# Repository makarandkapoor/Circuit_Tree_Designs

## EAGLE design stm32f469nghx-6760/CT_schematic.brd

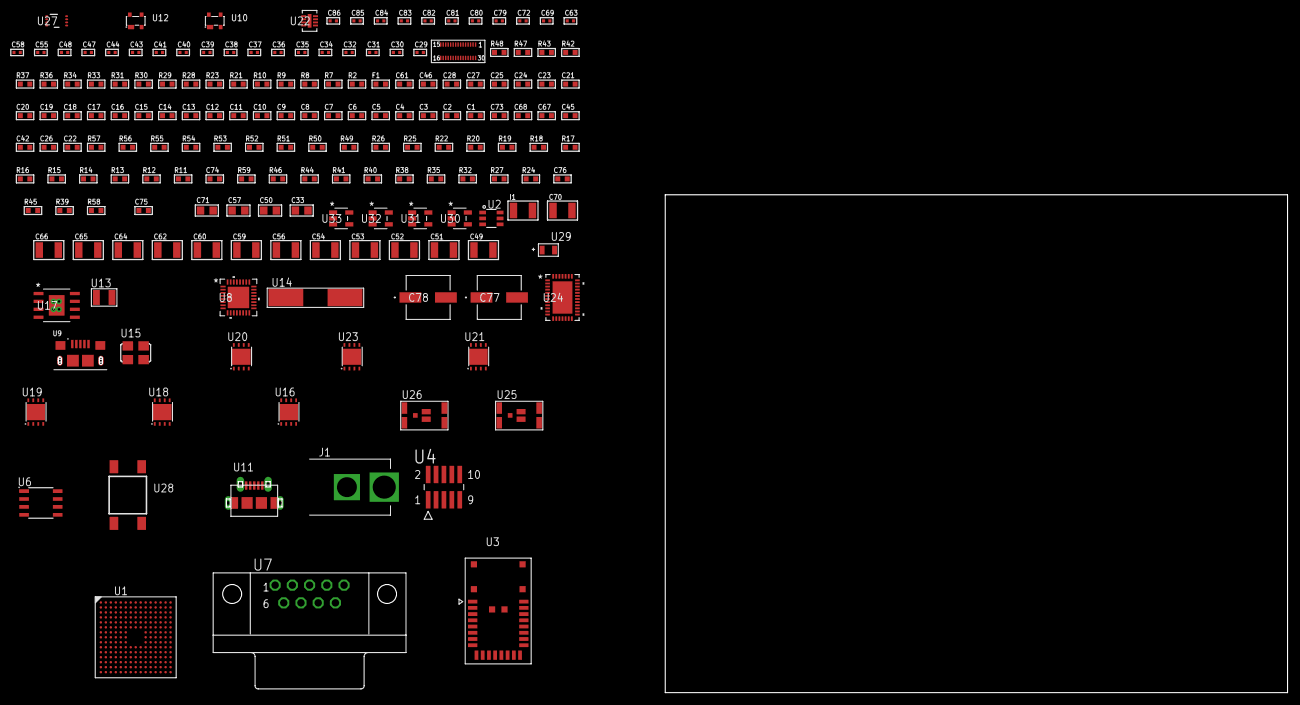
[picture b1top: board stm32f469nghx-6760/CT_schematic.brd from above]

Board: 2 copper layers, 176 parts (0 on the bottom side), 114 nets, no tracks yet.

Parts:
C1, C24, C46: 1e-06; C0603
C2, C3, C4, C5, C6, C7, C8, C9, C10, C11, C12, C13, C14, C15, C16, C17, C18, C19, C20, C21, C25, C27, C28: 1e-07; C0603
C22: 4.7e-06; C0603
C23: 1e-08; C0603
C26, C42, C45, C67, C73: 2.2e-06; C0603
C29, C30, C31, C32: 1e-11; C0402
C33, C50, C57, C71: 1e-05; C0805
C34, C35, C36, C37, C38, C39, C40, C41, C43, C44, C72, C80, C82: 1e-07; C0402
C47, C48, C55, C58, C63, C69, C79, C81, C83, C84, C85, C86: 1e-08; C0402
C49, C51, C52, C53, C54, C56, C59, C60, C62, C64, C65, C66, C70: 1e-05; C1210
C61: 8e-07; R0603
C68: 2.2e-07; C0603
C74: 2.45e-08; R0603
C75: 2.8258362168397e-09; R0603
C76: 7.105e-09; R0603
C77, C78: 0.0001; EXV-9H
F1: 240.0; L0603
I1: 1e-05; L1210
J1: PJ-037B; PJ-037B_PACKAGE
R2, R29, R34, R37, R43, R48: 1000.0; R0603
R7, R8, R9: 4700.0; R0603
R10, R31: 2200.0; R0603
R11: 47000.0; R0603
R12, R13, R14, R15, R16, R17, R18, R19, R20, R22, R25, R26, R49, R51, R52, R55, R56, R57: 10000.0; R0603
R21: 5.0; R0603
R23: 120.0; R0603
R24, R27, R32, R35, R38, R40, R41, R44, R46: 100000.0; R0603
R28, R47: 200.0; R0603
R30: 910.0; R0603
R33: 806.0; R0603
R36: 1800.0; R0603
R39: 153694.38; R0603
R42: 3900.0; R0603
R45: 1600000.0; R0603
R50: 75000.0; R0603
R53, R54: 95300.0; R0603
R58: 102454.54545455; R0603
R59: 200000.0; R0603
U1: STM32F469NGH6; TFBGA216
U2: MAX4995AAUT+T; SOT-23-6
U3: A2500R24A00GM
U4: FTSH-105-01-L-DV-K; SAMTEC_FTSH-105-01-L-DV-K
U5: LH430WV2-SD01
U6: SN65HVD230D; SOIC-8
U7: 182-009-113R531; 182-009-MALE
U8: TUSB1210BRHBR; RHB32_3P45X3P45
U9: 10118193-0001LF; FCI_10118193-0001LF
U10, U12: prtr5v0u2ax; SOT143B
U11: 47590-0001; MICRO_USB_AB
U13: ABS07-32.768KHZ-7-T
U14: ABLS-25.000MHZ-B2F-T
U15: ASFL1-26MHZ-NCS; ASFL1
U16, U18, U19, U21, U23: LP3878SDX-ADJ/NOPB; WSON-8
U17: MIC5234YME; SOIC-8_EP
U20: LP2951ACSDX/NOPB; WSON-8
U22: LT3494AEDDB#TRMPBF; DFN-8_DDB
U24: LTC2928CUHF#PBF; QFN-38_UHF
U25, U26: IRF8306MTRPbF; IRF8306MTRPBF
U27: LSF0102DCTR; DCU0008A_N
U28: 4-1437565-2; SW_4-1437565-2
U29: Q65110A2395; LGM67K-G1J2-24-Z
U30, U31, U32, U33: nc7sz125m5x; NC7SZ125M5X

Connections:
CLK_CRYSTAL_U1_E1: C29.1, U1.E1, U13.1
CLK_CRYSTAL_U1_F1: C30.1, U1.F1, U13.2
CLK_CRYSTAL_U1_G1: C31.1, U1.G1, U14.1
CLK_CRYSTAL_U1_H1: C32.1, U1.H1, U14.2
CLK_U8_1: U8.1, U15.3
GND: C1.2, C2.2, C3.2, C4.2, C5.2, C6.2, C7.2, C8.2, C9.2, C10.2, C11.2, C12.2, C13.2, C14.2, C15.2, C16.2, C17.2, C18.2, C19.2, C20.2, C21.2, C22.2, C23.2, C24.2, C25.2, C26.2, C27.2, C28.2, C29.2, C30.2, C31.2, C32.2, C33.2, C34.2, C35.2, C36.2, C37.2, C38.2, C39.2, C40.2, C41.2, C42.2, C43.2, C44.2, C45.2, C46.2, C47.2, C48.2, C49.2, C50.2, C51.2, C52.2, C53.2, C54.2, C55.2, C56.2, C57.2, C58.2, C59.2, C60.2, C61.2, C62.2, C63.2, C64.2, C65.2, C66.2, C67.2, C68.2, C69.2, C70.2, C71.2, C72.2, C73.2, C74.2, C75.2, C76.2, C77.2, C78.2, C79.2, C80.2, C81.2, C82.2, C83.2, C84.2, C85.2, C86.2, J1.2, R2.2, R11.2, R14.2, R17.2, R21.2, R22.2, R24.2, R29.2, R31.2, R34.2, R37.2, R40.2, R43.2, R48.2, R50.2, R53.2, R54.2, R55.2, R56.2, R57.2, U1.F2, U1.F6, U1.F7, U1.F8, U1.F9, U1.F10, U1.G6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
NET_U1_E5: R12.1, U1.E5
NET_U1_E6: R13.1, U1.E6
NET_U1_E11: C28.1, U1.E11
NET_U1_G13: C26.1, U1.G13, U1.K12
NET_U1_J1: R8.1, U1.J1, U32.4
NET_U1_L5: R15.1, U1.L5
NET_U1_M5: R14.1, U1.M5
NET_U1_R1: C23.1, C24.1, F1.1, U1.P1, U1.R1
NET_U1_R15: U28.3, U28.4
NET_U2_3: R11.1, U2.3
NET_U4_9: R21.1, U4.9
NET_U5_4: R7.1, U5.4, U31.4
NET_U5_20: R22.1, U5.20
NET_U6_6: R23.2, U6.6
NET_U6_8: R24.1, U6.8
NET_U7_2: R23.2, U6.6, U7.2
NET_U7_3: R23.1, U6.7, U7.3
NET_U8_11: R25.1, U8.11
NET_U8_12: C45.1, U8.12
NET_U8_14: R26.1, U8.14
NET_U8_20: C42.1, U8.20
NET_U8_27: R9.1, U8.27, U33.4
NET_U9_1: C46.1, U8.22, U9.1, U10.4
NET_U9_2: U8.19, U9.2, U10.3
NET_U9_3: U8.18, U9.3, U10.2
NET_U16_1: C48.1, U16.1
NET_U16_6: R28.2, R29.1, U16.6
NET_U16_8: R27.1, U16.8
NET_U17_4: R30.2, R31.1, U17.4
NET_U18_1: C55.1, U18.1
NET_U18_6: R33.2, R34.1, U18.6
NET_U18_8: R32.1, U18.8
NET_U19_1: C58.1, U19.1
NET_U19_6: R36.2, R37.1, U19.6
NET_U19_8: R35.1, U19.8
NET_U20_5: R38.1, U20.5
NET_U20_7: R39.2, R40.1, U20.7
NET_U21_1: C63.1, U21.1
NET_U21_6: R42.2, R43.1, U21.6
NET_U21_8: R41.1, U21.8
NET_U22_1: I1.1, U22.1
NET_U22_5: R44.1, U22.5
NET_U22_6: R45.1, U22.6
NET_U22_8: C68.1, U22.8
NET_U23_1: C69.1, U23.1
NET_U23_6: R47.2, R48.1, U23.6
NET_U23_8: R46.1, U23.8
NET_U24_3: R56.1, U24.3
NET_U24_6: R53.1, U24.6
NET_U24_7: R54.1, U24.7
NET_U24_16: R55.1, R58.1, U24.16
NET_U24_18: R52.1, U24.18
NET_U24_19: R51.1, U24.19, U24.20
NET_U24_21: R49.1, R50.1, U24.21, U30.4, U31.2, U32.2, U33.2
NET_U24_22: C72.1, R49.2, R51.2, R52.2, U24.11, U24.22
NET_U24_26: C75.1, U24.26
NET_U24_27: C74.1, U24.27
NET_U24_28: C76.1, U24.28
NET_U24_38: R57.1, U24.38
NET_U25_3: U24.2, U25.3
NET_U26_3: U24.37, U26.3
NET_U27_8: R59.1, U27.8
NET_U28_1: R2.1, U28.1, U28.2
PROC_CAN1_RX_TOXCVR: U6.4, U27.5
PROC_CAN1_TX_TOXCVR: U6.1, U27.6
PROC_DSIHOST_CKN: U1.H13, U5.13
PROC_DSIHOST_CKP: U1.H12, U5.14
PROC_DSIHOST_D0N: U1.J13, U5.7
PROC_DSIHOST_D0P: U1.J12, U5.8
PROC_DSIHOST_D1N: U1.F13, U5.10
PROC_DSIHOST_D1P: U1.F12, U5.11
PROC_GPIO_TO_U1_USB_FAULT: R16.1, U1.A2, U2.6
PROC_GPIO_TO_U1_VBUS_EN: R17.1, U1.A1, U2.4
PROC_SPI2_MISO: U1.C14, U3.10
PROC_SPI2_MOSI: U1.C13, U3.11
PROC_SPI2_NSS: U1.E14, U3.12
PROC_SPI2_SCK: U1.C11, U3.9
PROC_SYS_JTCK_SWCLK: R19.1, U1.A14, U4.4
PROC_SYS_JTDO_SWO: U1.A10, U4.6
PROC_SYS_JTMS_SWDIO: R20.1, U1.A15, U4.2
PROC_USB_OTG_FS_DM: U1.C15, U11.2, U12.3
PROC_USB_OTG_FS_DP: U1.B15, U11.3, U12.2
PROC_USB_OTG_FS_ID: U1.D15, U11.4
PROC_USB_OTG_FS_VBUS: U1.E15, U2.1, U11.1, U12.4
PROC_USB_OTG_HS_ULPI_CK: U1.P4, U8.26
PROC_USB_OTG_HS_ULPI_D0: U1.R2, U8.3
PROC_USB_OTG_HS_ULPI_D1: U1.R5, U8.4
PROC_USB_OTG_HS_ULPI_D2: U1.R4, U8.5
PROC_USB_OTG_HS_ULPI_D3: U1.P12, U8.6
PROC_USB_OTG_HS_ULPI_D4: U1.R13, U8.7
PROC_USB_OTG_HS_ULPI_D5: U1.L13, U8.9
PROC_USB_OTG_HS_ULPI_D6: U1.K14, U8.10
PROC_USB_OTG_HS_ULPI_D7: U1.A8, U8.13
PROC_USB_OTG_HS_ULPI_DIR: U1.F3, U8.31
PROC_USB_OTG_HS_ULPI_NXT: U1.H4, U8.2
PROC_USB_OTG_HS_ULPI_STP: U1.M2, U8.29
RST_OUT_U4_JTAG_RST_B: R18.1, U4.10, U30.1
VCC_12V6: C73.1, C77.1, C78.1, J1.1, R58.2, U24.23, U25.1, U25.2, U25.6, U25.7, U26.1, U26.2, U26.6, U26.7
VCC_S1_12V6: C49.1, C51.1, C52.1, C56.1, C59.1, C61.1, C64.1, C66.1, I1.2, R27.2, R32.2, R35.2, R41.2, R44.2, U16.4, U17.5, U17.8, U18.4, U19.4, U20.8, U21.4, U22.3, U22.4, U25.4, U25.5
VCC_S2_12V6: C70.1, R46.2, U23.4, U26.4, U26.5
VCC_TIER1_1V2: C27.1, C50.1, R28.1, U1.L11, U16.5
VCC_TIER1_1V5: C53.1, C54.1, R30.1, U5.29, U17.1
VCC_TIER1_1V8: C1.1, C2.1, C3.1, C4.1, C5.1, C6.1, C7.1, C8.1, C9.1, C10.1, C11.1, C12.1, C13.1, C14.1, C15.1, C16.1, C17.1, C18.1, C19.1, C20.1, C21.1, C22.1, C25.1, C33.1, C34.1, C35.1, C43.1, C44.1, C57.1, C81.1, C82.1, C83.1, C84.1, C85.1, C86.1, F1.2, R7.2, R8.2, R9.2, R10.2, R12.2, R13.2, R15.2, R16.2, R18.2, R19.2, R20.2, R25.2, R26.2, R33.1, U1.C1, U1.E7, U1.E8, U1.E9, U1.E10, U1.F4, U1.F5, U1.F11, U1.G5, U1.G11, U1.H5, U1.H11, U1.J5, U1.J11, U1.K5, U1.K11, U1.L7, U1.L8, U1.L9, U1.L10, U3.18, U4.1, U5.2, U8.28, U8.30, U8.32, U18.5, U27.2, U30.5, U31.5, U32.5, U33.5
VCC_TIER1_2V8: C37.1, C38.1, C39.1, C41.1, C60.1, R36.1, U5.16, U5.21, U5.22, U5.23, U8.21, U19.5
VCC_TIER1_3V3: C40.1, C47.1, C62.1, C79.1, C80.1, R38.2, R39.1, R59.2, U6.3, U15.4, U20.1, U27.7
VCC_TIER1_5V0: C65.1, R42.1, U2.5, U21.5
VCC_TIER1_12V0: C36.1, C67.1, R45.2, U5.30, U22.7
VCC_TIER2_1V2: C71.1, R47.1, U23.5

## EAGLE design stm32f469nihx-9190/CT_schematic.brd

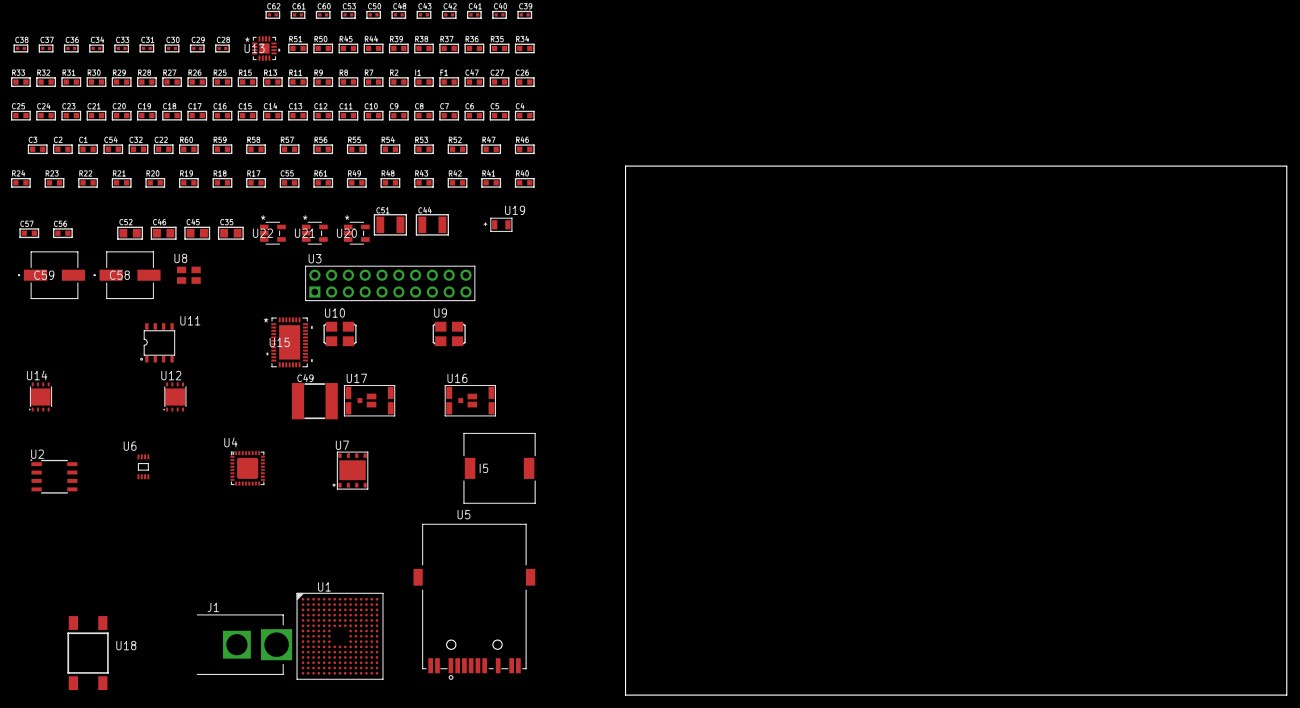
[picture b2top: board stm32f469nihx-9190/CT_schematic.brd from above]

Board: 2 copper layers, 100.0 x 80.0 mm, 140 parts (0 on the bottom side), 95 nets, no tracks yet.

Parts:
C1, C24, C47: 1e-06; C0603
C2, C3, C4, C5, C6, C7, C8, C9, C10, C11, C12, C13, C14, C15, C16, C17, C18, C19, C20, C21, C25, C26, C27: 1e-07; C0603
C22: 4.7e-06; C0603
C23: 1e-08; C0603
C28, C37, C39, C40, C41, C42, C43, C50, C60, C61, C62: 1e-08; C0402
C29, C30, C31, C33, C34, C36, C38, C48, C53: 1e-07; C0402
C32, C54: 2.2e-06; C0603
C35, C45, C46, C52: 1e-05; C0805
C44, C51: 1e-05; C1210
C49: 6.8e-05; 2220
C55: 2.45e-08; R0603
C56: 2.8258362168397e-09; R0603
C57: 7.105e-09; R0603
C58, C59: 0.0001; EXV-9H
F1: 240.0; L0603
I1: 97.0; R0603
I5: 5.2e-06; DR1040
J1: PJ-037B; PJ-037B_PACKAGE
R2, R34, R36, R37, R38, R39, R45, R51: 1000.0; R0603
R7, R8, R30, R31, R32, R33, R35: 4700.0; R0603
R9, R11, R13, R15: 2200.0; R0603
R17, R18, R19, R20, R21, R22, R23, R24, R52, R54, R55, R58, R59, R60: 10000.0; R0603
R25, R26: 0.1; R0603
R27, R44, R50: 200.0; R0603
R28: 220.0; R0603
R29: 6490.0; R0603
R40, R41, R42, R43, R49: 100000.0; R0603
R46: 20000.0; R0603
R47: 91000.0; R0603
R48: 300000.0; R0603
R53: 75000.0; R0603
R56, R57: 95300.0; R0603
R61: 110000.0; R0603
U1: STM32F469NIH6; TFBGA216
U2: AT25512N-SH-T; SOIC-8
U3: TST-110-05-T-D-RA
U4: KSZ8081RNBIA-TR; QFN-32
U5: 7498011122R
U6: 24AA02T-I/MNY; TDFN-8/6MM
U7: SST26VF064B-104I/MF; WFDN-8
U8: ASEK-32.768KHz-ECST; ASEK
U9: ASFL1-25MHZ-NCS; ASFL1
U10: ASFL1-50MHZ-NCS; ASFL1
U11: idt74fct38072; IDT74FCT38072
U12, U14: LP3878SDX-ADJ/NOPB; WSON-8
U13: LTC3601EUD#PBF; QFN-16_EP
U15: LTC2928CUHF#PBF; QFN-38_UHF
U16, U17: IRF8306MTRPbF; IRF8306MTRPBF
U18: 4-1437565-2; SW_4-1437565-2
U19: Q65110A2395; LGM67K-G1J2-24-Z
U20, U21, U22: nc7sz125m5x; NC7SZ125M5X

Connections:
CLK_U1_E1: U1.E1, U8.3
CLK_U1_G1: U1.G1, U9.3
CLK_U1_N2: U1.N2, U11.7
CLK_U4_9: U4.9, U11.6
CLK_U11_3: U10.3, U11.3
GND: C1.2, C2.2, C3.2, C4.2, C5.2, C6.2, C7.2, C8.2, C9.2, C10.2, C11.2, C12.2, C13.2, C14.2, C15.2, C16.2, C17.2, C18.2, C19.2, C20.2, C21.2, C22.2, C23.2, C24.2, C25.2, C26.2, C27.2, C28.2, C29.2, C30.2, C31.2, C32.2, C33.2, C34.2, C35.2, C36.2, C37.2, C38.2, C39.2, C40.2, C41.2, C42.2, C43.2, C44.2, C45.2, C46.2, C47.2, C49.1, C49.2, C50.2, C51.2, C52.2, C53.2, C54.2, C55.2, C56.2, C57.2, C58.2, C59.2, C60.2, C61.2, C62.2, J1.2, R2.2, R19.2, R25.2, R26.2, R29.2, R31.2, R34.2, R36.2, R37.2, R38.2, R39.2, R45.2, R46.2, R48.2, R51.2, R53.2, R56.2, R57.2, R58.2, R59.2, R60.2, U1.F2, U1.F6, U1.F7, U1.F8, U1.F9, U1.F10, U1.G6, U1.G10, U1.G12, U1.H6, U1.H10, U1.J6, U1.J10, U1.K6, U1.K7, U1.K8, U1.K9, U1.K10, U1.L6, U1.M1, U1.N1, U2.4, U3.4, U3.6, U3.8, U3.10, U3.12, U3.14, U3.16, U3.18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
NET_U1_A7: R9.1, U1.A7, U6.6
NET_U1_B4: R11.1, U1.B4, U6.5
NET_U1_E5: R17.1, U1.E5
NET_U1_E6: R18.1, U1.E6
NET_U1_E11: C27.1, U1.E11
NET_U1_J1: R8.1, U1.J1, U22.4
NET_U1_L5: R20.1, U1.L5
NET_U1_M3: R13.1, U1.M3, U4.12
NET_U1_M5: R19.1, U1.M5
NET_U1_P2: R15.1, U1.P2, U4.11
NET_U1_R1: C23.1, C24.1, F1.1, U1.P1, U1.R1
NET_U1_R15: U18.3, U18.4
NET_U2_3: R21.1, U2.3
NET_U2_7: R23.1, U2.7
NET_U4_2: C32.1, C33.1, U4.2
NET_U4_3: C34.1, I1.1, U4.3
NET_U4_10: R29.1, U4.10
NET_U4_13: R32.1, U4.13
NET_U4_14: R33.1, U4.14
NET_U4_19: R31.1, U4.19
NET_U4_20: R37.1, U4.20
NET_U4_21: R30.1, U4.21
NET_U4_28: R35.1, U4.28
NET_U4_29: R36.1, U4.29
NET_U4_31: R38.1, U4.31
NET_U4_32: R7.1, U4.32, U21.4
NET_U5_1: U4.7, U5.1
NET_U5_2: C30.1, U5.2
NET_U5_3: U4.6, U5.3
NET_U5_4: U4.5, U5.4
NET_U5_5: C31.1, U5.5
NET_U5_6: U4.4, U5.6
NET_U5_8: R26.1, U5.8
NET_U5_9: R27.1, U5.9
NET_U5_12: R28.1, U5.12
NET_U5_13: R25.1, U5.13, U5.14
NET_U12_1: C43.1, U12.1
NET_U12_6: R44.2, R45.1, U12.6
NET_U12_8: R43.1, U12.8
NET_U13_3: C48.2, I5.1, U13.3, U13.4
NET_U13_6: C48.1, U13.6
NET_U13_7: C47.1, U13.7, U13.12
NET_U13_10: R48.1, U13.10
NET_U13_11: R46.1, R47.1, U13.11
NET_U13_ATNET_3: I5.2, R47.2
NET_U14_1: C50.1, U14.1
NET_U14_6: R50.2, R51.1, U14.6
NET_U14_8: R49.1, U14.8
NET_U15_3: R59.1, U15.3
NET_U15_6: R56.1, U15.6
NET_U15_7: R57.1, U15.7
NET_U15_16: R58.1, R61.1, U15.16
NET_U15_18: R55.1, U15.18
NET_U15_19: R54.1, U15.19, U15.20
NET_U15_21: R52.1, R53.1, U15.21, U20.4, U21.2, U22.2
NET_U15_22: C53.1, R52.2, R54.2, R55.2, U15.11, U15.22
NET_U15_26: C56.1, U15.26
NET_U15_27: C55.1, U15.27
NET_U15_28: C57.1, U15.28
NET_U15_38: R60.1, U15.38
NET_U16_3: U15.2, U16.3
NET_U17_3: U15.37, U17.3
NET_U18_1: R2.1, U18.1, U18.2
PROC_ETH_CRS_DV: U1.R3, U4.18
PROC_ETH_RXD0: R39.1, U1.N5, U4.16
PROC_ETH_RXD1: R34.1, U1.P5, U4.15
PROC_ETH_TXD0: U1.B3, U4.24
PROC_ETH_TXD1: U1.A4, U4.25
PROC_ETH_TX_EN: U1.B8, U4.23
PROC_QUADSPI_BK1_IO0: U1.F14, U7.5
PROC_QUADSPI_BK1_IO1: U1.B14, U7.2
PROC_QUADSPI_BK1_IO2: R41.1, U1.A3, U7.3
PROC_QUADSPI_BK1_IO3: R42.1, U1.K2, U7.7
PROC_QUADSPI_BK1_NCS: R40.1, U1.B6, U7.1
PROC_QUADSPI_CLK: U1.L1, U7.6
PROC_SPI1_MISO: U1.A9, U2.2
PROC_SPI1_MOSI: U1.A8, U2.5
PROC_SPI1_NSS: R22.1, U1.A13, U2.1
PROC_SPI1_SCK: U1.P4, U2.6
PROC_SYS_JTCK_SWCLK: U1.A14, U3.9
PROC_SYS_JTDO_SWO: U1.A10, U3.13
PROC_SYS_JTMS_SWDIO: U1.A15, U3.7
RST_OUT_U3_SRESET_B: R24.1, U3.15, U20.1
VCC_13V3: C54.1, C58.1, C59.1, J1.1, R61.2, U15.23, U16.1, U16.2, U16.6, U16.7, U17.1, U17.2, U17.6, U17.7
VCC_S1_13V3: C44.1, C46.1, R43.2, U12.4, U13.15, U13.16, U16.4, U16.5
VCC_S2_13V3: C51.1, R49.2, U14.4, U17.4, U17.5
VCC_TIER1_1V2: C26.1, C45.1, R44.1, U1.L11, U12.5
VCC_TIER1_3V3: C1.1, C2.1, C3.1, C4.1, C5.1, C6.1, C7.1, C8.1, C9.1, C10.1, C11.1, C12.1, C13.1, C14.1, C15.1, C16.1, C17.1, C18.1, C19.1, C20.1, C21.1, C22.1, C25.1, C28.1, C29.1, C35.1, C36.1, C37.1, C38.1, C39.1, C40.1, C41.1, C42.1, C49.2, C60.1, C61.1, C62.1, F1.2, I1.2, I5.2, R7.2, R8.2, R9.2, R11.2, R13.2, R15.2, R17.2, R18.2, R20.2, R21.2, R22.2, R23.2, R24.2, R30.2, R32.2, R33.2, R35.2, R40.2, R41.2, R42.2, R47.2, U1.C1, U1.E7, U1.E8, U1.E9, U1.E10, U1.F4, U1.F5, U1.F11, U1.G5, U1.G11, U1.H5, U1.H11, U1.J5, U1.J11, U1.K5, U1.K11, U1.L7, U1.L8, U1.L9, U1.L10, U2.8, U3.1, U4.17, U6.8, U7.8, U8.4, U9.4, U10.4, U11.1, U11.2, U13.8, U20.5, U21.5, U22.5
VCC_TIER2_1V2: C52.1, R50.1, U14.5

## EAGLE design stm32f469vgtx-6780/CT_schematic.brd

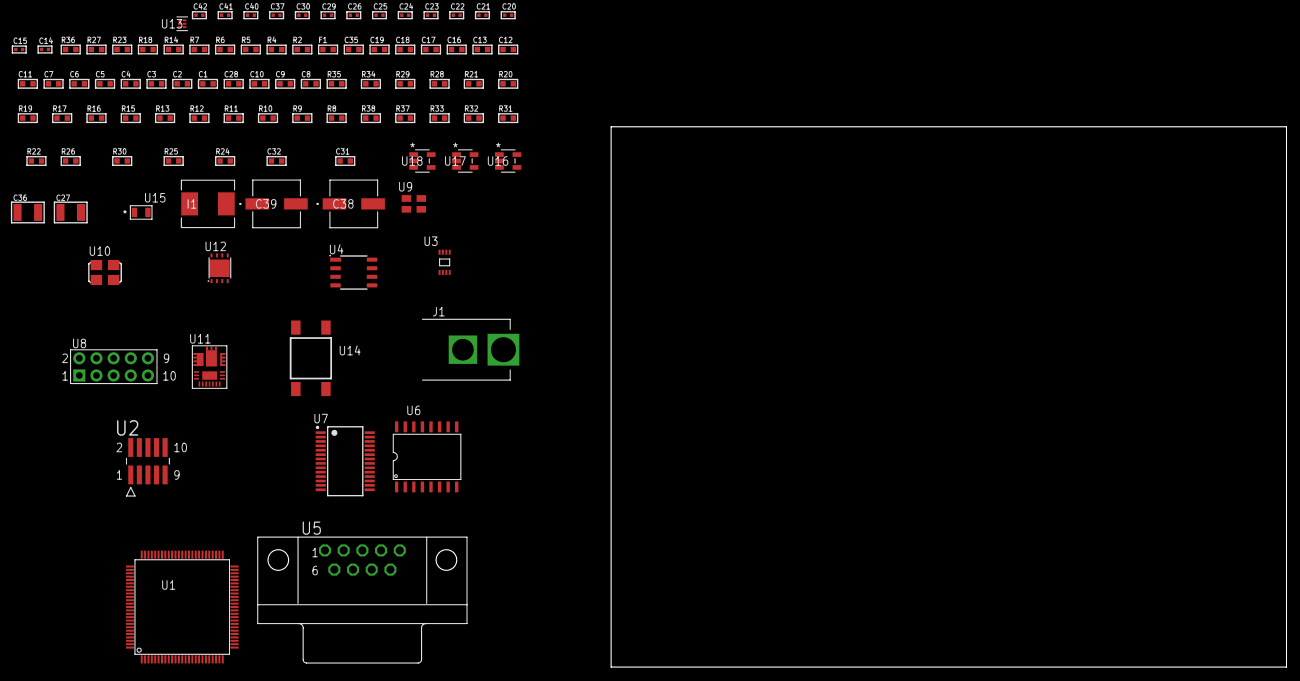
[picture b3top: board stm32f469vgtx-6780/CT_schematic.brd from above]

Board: 2 copper layers, 100.0 x 80.0 mm, 97 parts (0 on the bottom side), 65 nets, no tracks yet.

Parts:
C1, C12, C16, C17, C18, C19: 1e-06; C0603
C2, C3, C4, C5, C6, C7, C13: 1e-07; C0603
C8: 4.7e-06; C0603
C9, C10, C28: 2.2e-06; C0603
C11: 1e-08; C0603
C14, C20, C21, C22, C23, C24, C29, C30, C37: 1e-07; C0402
C15, C25, C26, C40, C41, C42: 1e-08; C0402
C27: 0.0001; C1210
C31: 8.7488758840791e-09; R0603
C32: 2.9825713241179e-07; R0603
C35: 8e-07; R0603
C36: 1e-05; C1210
C38, C39: 0.0001; EXV-9H
F1: 240.0; L0603
I1: 6.8e-07; IND25X25CZ
J1: PJ-037B; PJ-037B_PACKAGE
R2: 1000.0; R0603
R4, R5: 4700.0; R0603
R6, R7: 2200.0; R0603
R8, R9, R10, R11, R12, R13, R15, R16, R17, R19, R20, R21, R34, R35: 10000.0; R0603
R14: 5.0; R0603
R18: 120.0; R0603
R22, R31, R33: 100000.0; R0603
R23: 0.1; R0603
R24: 4030.2416170974; R0603
R25: 719.68600305311; R0603
R26: 58.26650887574; R0603
R27: 130.0; R0603
R28: 39000.0; R0603
R29: 49900.0; R0603
R30: 5113.9346405229; R0603
R32: 300000.0; R0603
R36: 9100.0; R0603
R37: 680000.0; R0603
R38: 120000.0; R0603
U1: STM32F469VGT6; LQFP100
U2: FTSH-105-01-L-DV-K; SAMTEC_FTSH-105-01-L-DV-K
U3: 24AA128T-I/MNY; TDFN-8/6MM
U4: MCP2562-E/SN; SOIC-8
U5: 182-009-113R531; 182-009-MALE
U6: S25FL128SDSMFI000
U7: ST3241EBPR; SSOP-28
U8: HTSS-105-01-G-D
U9: ASEK-32.768KHz-ECST; ASEK
U10: ASFL1-25MHZ-NCS; ASFL1
U11: IR3899MTR1PBF
U12: LP2951ACSDX/NOPB; WSON-8
U13: TPS3895ADRYR; SON-6
U14: 4-1437565-2; SW_4-1437565-2
U15: Q65110A2395; LGM67K-G1J2-24-Z
U16, U17, U18: nc7sz125m5x; NC7SZ125M5X

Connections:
CLK_U1_5: U1.5, U9.3
CLK_U1_9: U1.9, U10.3
GND: C1.2, C2.2, C3.2, C4.2, C5.2, C6.2, C7.2, C8.2, C9.2, C10.2, C11.2, C12.2, C13.2, C14.2, C15.2, C16.2, C17.2, C18.2, C19.2, C20.2, C23.2, C24.2, C25.2, C26.2, C28.2, C29.2, C30.2, C35.2, C36.2, C37.2, C38.2, C39.2, C40.2, C41.2, C42.2, J1.2, R2.2, R13.2, R14.2, R17.2, R23.1, R23.2, R25.2, R28.2, R30.2, R33.2, R36.2, R38.2, U1.2, U1.7, U1.16, U1.23, U1.44, U1.59, U1.78, U2.3, U2.5, U3.4, U4.2, U4.8, U5.5, U6.10, U7.23, U7.25, U8.9, U9.2, U10.2, U11.4, U11.11, U11.17, U12.3, U12.4, U12.PAD, U13.2, U15.C, U16.2, U16.3, U17.1, U17.3, U18.1, U18.3
NET_U1_11: R5.1, U1.11, U18.4
NET_U1_18: C11.1, C12.1, F1.1, U1.17, U1.18
NET_U1_31: R9.1, U1.31
NET_U1_43: C9.1, U1.43
NET_U1_76: C10.1, U1.76
NET_U1_95: R6.1, U1.95, U3.6
NET_U1_96: R7.1, U1.96, U3.5
NET_U1_97: R8.1, U1.97
NET_U1_99: U14.3, U14.4
NET_U2_9: R14.1, U2.9
NET_U3_1: R15.1, U3.1
NET_U3_2: R16.1, U3.2
NET_U3_3: R17.1, U3.3
NET_U4_6: R18.2, U4.6
NET_U5_2: R18.2, U4.6, U5.2
NET_U5_3: R18.1, U4.7, U5.3
NET_U6_3: R4.1, U6.3, U17.4
NET_U7_1: C22.1, U7.1
NET_U7_2: C22.2, U7.2
NET_U7_3: C24.1, U7.3
NET_U7_22: R22.1, U7.22
NET_U7_24: C21.2, U7.24
NET_U7_27: C23.1, U7.27
NET_U7_28: C21.1, U7.28
NET_U8_3: U7.4, U8.3
NET_U8_4: U7.5, U8.4
NET_U8_5: U7.9, U8.5
NET_U8_6: U7.10, U8.6
NET_U11_1: C31.1, R24.1, R25.1, R26.1, R27.1, U11.1, U11.8
NET_U11_2: C30.1, U11.2
NET_U11_3: C31.2, C32.1, C32.2, U11.3
NET_U11_5: R28.1, U11.5
NET_U11_10: C28.1, U11.10
NET_U11_12: C27.1, I1.1, U11.12
NET_U11_14: C27.2, U11.14
NET_U11_15: R29.1, R30.1, U11.15
NET_U11_ATNET_3: I1.2, R24.2
NET_U11_ATNET_4: C32.2, R26.2
NET_U12_5: R31.1, U12.5
NET_U12_7: R32.2, R33.1, U12.7
NET_U13_1: R35.1, R36.1, U13.1
NET_U13_3: R37.2, R38.1, U13.3
NET_U13_4: R34.1, U13.4, U16.4, U17.2, U18.2
NET_U14_1: R2.1, U14.1, U14.2
PROC_CAN1_RX: U1.73, U4.4
PROC_CAN1_TX: U1.74, U4.1
PROC_QUADSPI_BK1_IO0: U1.69, U6.15
PROC_QUADSPI_BK1_IO1: U1.81, U6.8
PROC_QUADSPI_BK1_IO2: R20.1, U1.1, U6.9
PROC_QUADSPI_BK1_IO3: R21.1, U1.20, U6.1
PROC_QUADSPI_BK1_NCS: R19.1, U1.41, U6.7
PROC_QUADSPI_CLK: U1.28, U6.16
PROC_SYS_JTCK_SWCLK: R13.1, U1.79, U2.4
PROC_SYS_JTDI: R11.1, U1.80, U2.8
PROC_SYS_JTDO_SWO: U1.92, U2.6
PROC_SYS_JTMS_SWDIO: R12.1, U1.75, U2.2
PROC_UART4_RX: U1.82, U7.19
PROC_UART4_TX: U1.19, U7.14
RST_OUT_U2_JTAG_RST_B: R10.1, U2.10, U16.1
VCC_S1_16V9: C29.1, C35.1, C38.1, C39.1, J1.1, R29.2, U11.9, U12.8
VCC_TIER1_3V3: C1.1, C2.1, C3.1, C4.1, C5.1, C6.1, C7.1, C8.1, C13.1, C14.1, C15.1, C17.1, C18.1, C19.1, C20.1, C25.1, C26.1, C37.1, C40.1, C41.1, C42.1, F1.2, I1.2, R4.2, R5.2, R6.2, R7.2, R8.2, R9.2, R10.2, R11.2, R12.2, R15.2, R16.2, R19.2, R20.2, R21.2, R22.2, R24.2, R34.2, R35.2, R37.1, U1.3, U1.8, U1.24, U1.45, U1.55, U1.65, U1.77, U1.100, U2.1, U3.7, U3.8, U4.5, U6.2, U6.14, U7.26, U9.4, U10.4, U13.6, U16.5, U17.5, U18.5
VCC_TIER1_5V0: C16.1, C36.1, R31.2, R32.1, U4.3, U12.1

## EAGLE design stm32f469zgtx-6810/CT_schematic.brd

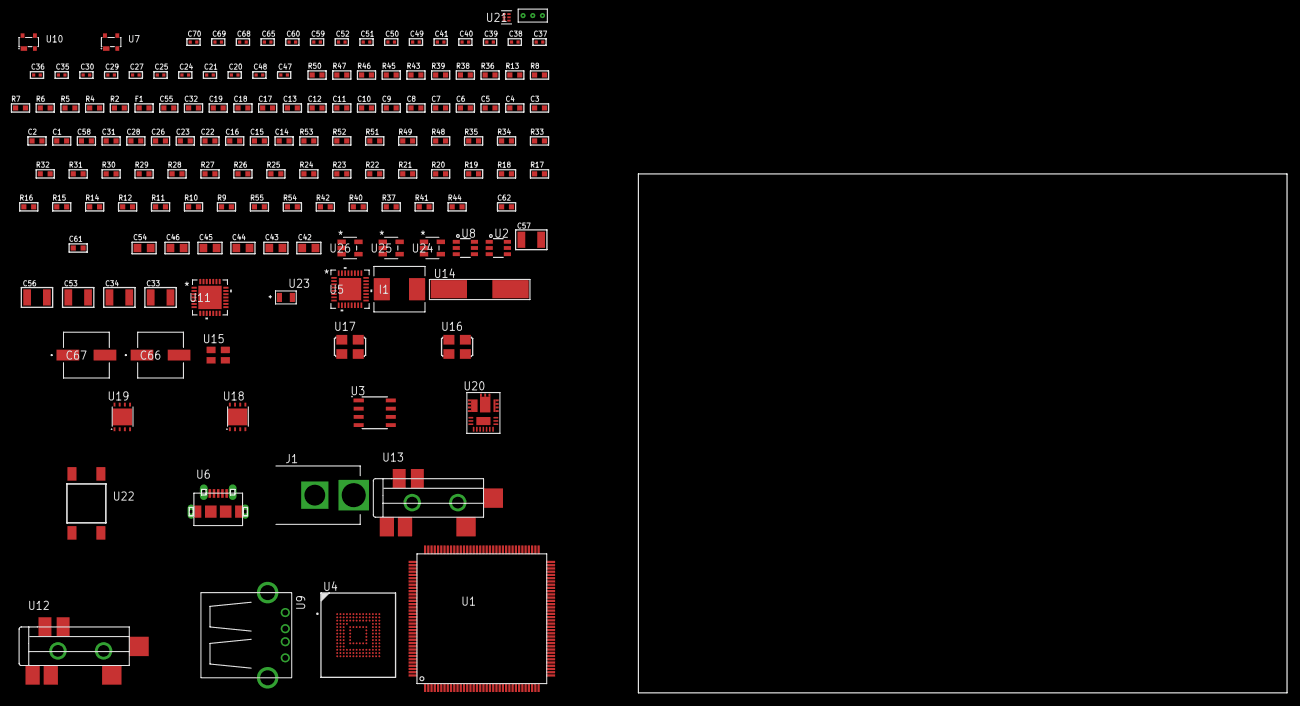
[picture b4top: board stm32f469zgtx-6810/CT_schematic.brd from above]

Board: 2 copper layers, 151 parts (0 on the bottom side), 95 nets, no tracks yet.

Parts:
C1, C18, C32: 1e-06; C0603
C2, C3, C4, C5, C6, C7, C8, C9, C10, C11, C12, C13, C19: 1e-07; C0603
C14: 4.7e-06; C0603
C15, C16, C22, C23, C26, C28, C31, C58: 2.2e-06; C0603
C17: 1e-08; C0603
C20, C49, C50, C51, C52, C68, C69, C70: 1e-08; C0402
C21, C24, C25, C27, C29, C30, C37, C38, C39, C40, C41, C59, C60, C65: 1e-07; C0402
C33, C34: 2.2e-05; C1210
C35, C36: 1e-09; C0402
C42, C43, C44, C45, C46, C54: 1e-05; C0805
C47, C48: 2.2e-11; C0402
C53, C56: 1e-05; C1210
C55: 8e-07; R0603
C57: 0.0001; C1210
C61: 6.9430689229727e-09; R0603
C62: 2.3669553146498e-07; R0603
C66, C67: 0.0001; EXV-9H
F1: 240.0; L0603
I1: 6.8e-07; IND25X25CZ
J1: PJ-037B; PJ-037B_PACKAGE
R2, R39: 1000.0; R0603
R4, R5, R6: 4700.0; R0603
R7, R8: 2200.0; R0603
R9, R30, R33, R34, R35: 47000.0; R0603
R10, R11, R12, R14, R15, R16, R17, R18, R19, R31, R32, R51, R52: 10000.0; R0603
R13: 1270.0; R0603
R20, R21, R22, R23, R24, R25, R26, R27, R28, R29: 34000.0; R0603
R36: 680.0; R0603
R37, R40, R42: 100000.0; R0603
R38: 806.0; R0603
R41: 153694.38; R0603
R43: 0.1; R0603
R44: 4030.2416170974; R0603
R45: 453.0; R0603
R46: 75.0; R0603
R47: 130.0; R0603
R48: 39000.0; R0603
R49: 49900.0; R0603
R50: 5760.0; R0603
R53: 82000.0; R0603
R54: 300000.0; R0603
R55: 120000.0; R0603
U1: STM32F469ZGT6; LQFP144
U2, U8: MAX4995AAUT+T; SOT-23-6
U3: AT24C02D-SSHM-T; AT24C02D
U4: mtfc4gmcdm; TFBGA-153
U5: TUSB1210BRHBR; RHB32_3P45X3P45
U6: 47590-0001; MICRO_USB_AB
U7, U10: prtr5v0u2ax; SOT143B
U9: 61400416021; USB-A-H
U11: WM8731CLSEFL; QFN-28
U12, U13: SJ-43515TS-SMT-TR
U14: ABLS-12.288MHZ-B4-T
U15: ASEK-32.768KHz-ECST; ASEK
U16: ASFL1-19.2MHZ-NCS; ASFL1
U17: ASFL1-25MHZ-NCS; ASFL1
U18: LP3878SDX-ADJ/NOPB; WSON-8
U19: LP2951ACSDX/NOPB; WSON-8
U20: IR3899MTR1PBF
U21: TPS3895ADRYR; SON-6
U22: 4-1437565-2; SW_4-1437565-2
U23: Q65110A2395; LGM67K-G1J2-24-Z
U24, U25, U26: nc7sz125m5x; NC7SZ125M5X
U27: Dummy; DUMMY_PACKAGE_331

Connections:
CLK_CRYSTAL_U11_1: C47.1, U11.1, U14.1
CLK_CRYSTAL_U11_2: C48.1, U11.2, U14.2
CLK_U1_7: U1.7, U15.3
CLK_U1_18: U1.18, U17.3
CLK_U5_1: U5.1, U16.3
GND: C1.2, C2.2, C3.2, C4.2, C5.2, C6.2, C7.2, C8.2, C9.2, C10.2, C11.2, C12.2, C13.2, C14.2, C15.2, C16.2, C17.2, C18.2, C19.2, C20.2, C21.2, C22.2, C23.2, C24.2, C25.2, C26.2, C27.2, C28.2, C29.2, C30.2, C31.2, C32.2, C36.2, C37.2, C38.2, C39.2, C40.2, C41.2, C42.2, C43.2, C44.2, C45.2, C46.2, C47.2, C48.2, C49.2, C50.2, C51.2, C52.2, C53.2, C54.2, C55.2, C56.2, C58.2, C59.2, C60.2, C65.2, C66.2, C67.2, C68.2, C69.2, C70.2, J1.2, R2.2, R9.2, R13.2, R15.2, R16.2, R18.2, R19.2, R30.2, R32.2, R33.2, R34.2, R35.2, R39.2, R42.2, R43.1, R43.2, R45.2, R48.2, R50.2, R53.2, R55.2, U1.15, U1.26, U1.33, U1.55, U1.76, U1.84, U1.109, U1.122, U1.129, U2.2, U3.4, U4.C4, U4.E7, U4.G5, U4.H10, U4.K8, U4.N2, U4.N5, U4.P4, U4.P6, U5.33, U6.5, U6.6, U6.7, U6.8, U6.9, U7.1, U8.2, U9.4, U9.5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
NET_U1_20: R5.1, U1.20, U25.4
NET_U1_28: C17.1, C18.1, F1.1, U1.27, U1.28
NET_U1_43: R12.1, U1.43
NET_U1_65: C15.1, U1.65
NET_U1_104: R13.1, U1.104
NET_U1_108: C16.1, U1.108
NET_U1_135: R7.1, U1.135, U3.6
NET_U1_136: R8.1, U1.136, U3.5
NET_U1_137: R11.1, U1.137
NET_U1_142: R10.1, U1.142
NET_U1_144: U22.3, U22.4
NET_U2_3: R9.1, U2.3
NET_U3_1: R17.1, U3.1
NET_U3_2: R18.1, U3.2
NET_U3_3: R19.1, U3.3
NET_U3_7: R16.1, U3.7
NET_U4_C2: C23.1, C24.1, U4.C2
NET_U4_K5: R4.1, U4.K5, U24.4
NET_U5_11: R31.1, U5.11
NET_U5_12: C31.1, U5.12
NET_U5_14: R32.1, U5.14
NET_U5_20: C28.1, U5.20
NET_U5_27: R6.1, U5.27, U26.4
NET_U6_1: C32.1, U5.22, U6.1, U7.4, U8.1
NET_U6_2: U5.19, U6.2, U7.3
NET_U6_3: U5.18, U6.3, U7.2
NET_U6_4: U5.23, U6.4
NET_U8_3: R30.1, U8.3
NET_U8_4: U5.17, U8.4
NET_U11_20: C41.1, C46.1, U11.20
NET_U12_2: C34.1, R34.1, U12.2
NET_U12_5: C33.1, R33.1, U12.5
NET_U13_5: C35.1, C36.1, R35.1, R36.1, U13.5
NET_U18_1: C52.1, U18.1
NET_U18_6: R38.2, R39.1, U18.6
NET_U18_8: R37.1, U18.8
NET_U19_5: R40.1, U19.5
NET_U19_7: R41.2, R42.1, U19.7
NET_U20_1: C61.1, R44.1, R45.1, R46.1, R47.1, U20.1, U20.8
NET_U20_2: C60.1, U20.2
NET_U20_3: C61.2, C62.1, C62.2, U20.3
NET_U20_5: R48.1, U20.5
NET_U20_10: C58.1, U20.10
NET_U20_12: C57.1, I1.1, U20.12
NET_U20_14: C57.2, U20.14
NET_U20_15: R49.1, R50.1, U20.15
NET_U20_ATNET_3: I1.2, R44.2
NET_U20_ATNET_4: C62.2, R46.2
NET_U21_1: R52.1, R53.1, U21.1
NET_U21_3: R54.2, R55.1, U21.3
NET_U21_4: R51.1, U21.4, U24.2, U25.2, U26.2
NET_U22_1: R2.1, U22.1, U22.2
PROC_ADC1_IN0: U1.29, U27.3
PROC_ADC1_IN2: U1.31, U27.2
PROC_GPIO_TO_U1_USB_FAULT: R14.1, U1.2, U2.6
PROC_GPIO_TO_U1_VBUS_EN: R15.1, U1.1, U2.4
PROC_I2S3_CK: U1.132, U11.7
PROC_I2S3_EXT_SD: U1.133, U11.10
PROC_I2S3_SD: U1.124, U11.8
PROC_I2S3_WS: U1.35, U11.9, U11.11
PROC_SDIO_CK: R29.1, U1.115, U4.M6
PROC_SDIO_CMD: R28.1, U1.118, U4.M5
PROC_SDIO_D0: R20.1, U1.100, U4.A3
PROC_SDIO_D1: R21.1, U1.101, U4.A4
PROC_SDIO_D2: R22.1, U1.113, U4.A5
PROC_SDIO_D3: R23.1, U1.114, U4.B2
PROC_SDIO_D4: R24.1, U1.138, U4.B3
PROC_SDIO_D5: R25.1, U1.139, U4.B4
PROC_SDIO_D6: R26.1, U1.98, U4.B5
PROC_SDIO_D7: R27.1, U1.99, U4.B6
PROC_USB_OTG_FS_DM: U1.105, U9.2, U10.3
PROC_USB_OTG_FS_DP: U1.106, U9.3, U10.2
PROC_USB_OTG_FS_VBUS: U1.103, U2.1, U9.1, U10.4
PROC_USB_OTG_HS_ULPI_CK: U1.36, U5.26
PROC_USB_OTG_HS_ULPI_D0: U1.32, U5.3
PROC_USB_OTG_HS_ULPI_D1: U1.41, U5.4
PROC_USB_OTG_HS_ULPI_D2: U1.42, U5.5
PROC_USB_OTG_HS_ULPI_D3: U1.63, U5.6
PROC_USB_OTG_HS_ULPI_D4: U1.64, U5.7
PROC_USB_OTG_HS_ULPI_D5: U1.67, U5.9
PROC_USB_OTG_HS_ULPI_D6: U1.68, U5.10
PROC_USB_OTG_HS_ULPI_D7: U1.134, U5.13
PROC_USB_OTG_HS_ULPI_DIR: U1.23, U5.31
PROC_USB_OTG_HS_ULPI_NXT: U1.24, U5.2
PROC_USB_OTG_HS_ULPI_STP: U1.21, U5.29
VCC_S1_15V2: C53.1, C55.1, C59.1, C66.1, C67.1, J1.1, R37.2, R49.2, U18.4, U19.8, U20.9
VCC_TIER1_1V8: C1.1, C2.1, C3.1, C4.1, C5.1, C6.1, C7.1, C8.1, C9.1, C10.1, C11.1, C12.1, C13.1, C14.1, C19.1, C20.1, C21.1, C22.1, C29.1, C30.1, C37.1, C38.1, C39.1, C40.1, C42.1, C43.1, C44.1, C45.1, C54.1, C65.1, C68.1, C69.1, C70.1, F1.2, R4.2, R5.2, R6.2, R7.2, R8.2, R10.2, R11.2, R12.2, R14.2, R17.2, R20.2, R21.2, R22.2, R23.2, R24.2, R25.2, R26.2, R27.2, R28.2, R29.2, R31.2, R38.1, R51.2, R52.2, R54.1, U1.5, U1.16, U1.25, U1.34, U1.46, U1.56, U1.66, U1.77, U1.80, U1.97, U1.110, U1.123, U1.130, U1.143, U3.8, U4.C6, U4.M4, U4.N4, U4.P3, U4.P5, U5.28, U5.30, U5.32, U11.3, U11.5, U11.12, U11.18, U18.5, U21.6, U24.5, U25.5, U26.5
VCC_TIER1_3V3: C25.1, C26.1, C27.1, C49.1, C50.1, C51.1, C56.1, R40.2, R41.1, U4.E6, U4.F5, U4.J10, U4.K9, U5.21, U15.4, U16.4, U17.4, U19.1
VCC_TIER1_5V0: I1.2, R44.2, U2.5, U8.5

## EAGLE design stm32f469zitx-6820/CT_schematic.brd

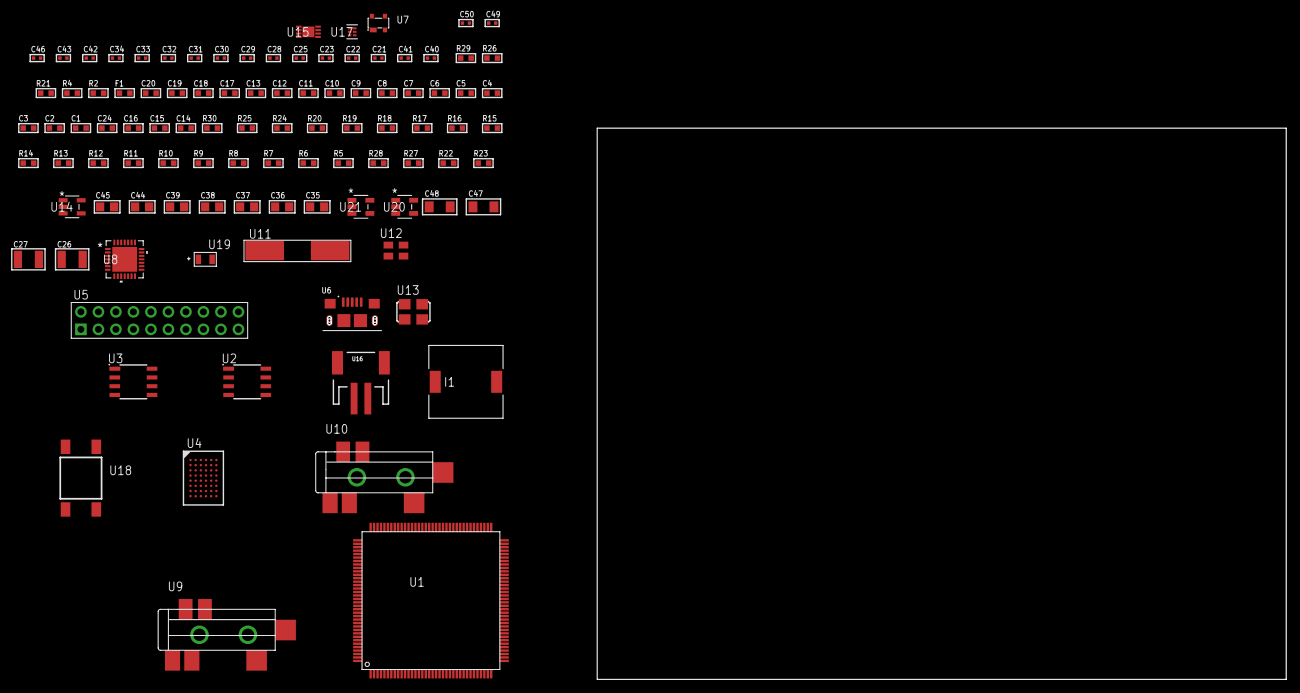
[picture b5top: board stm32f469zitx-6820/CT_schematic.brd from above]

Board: 2 copper layers, 101 parts (0 on the bottom side), 89 nets, no tracks yet.

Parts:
C1, C18, C20: 1e-06; C0603
C2, C3, C4, C5, C6, C7, C8, C9, C10, C11, C12, C13, C19: 1e-07; C0603
C14: 4.7e-06; C0603
C15, C16, C24: 2.2e-06; C0603
C17: 1e-08; C0603
C21, C22, C42, C43, C49, C50: 1e-08; C0402
C23, C25, C30, C31, C32, C33, C34, C46: 1e-07; C0402
C26, C27: 2.2e-05; C1210
C28, C29: 1e-09; C0402
C35, C36, C37, C38, C39, C44, C45: 1e-05; C0805
C40, C41: 2.2e-11; C0402
C47, C48: 1e-05; C1206
F1: 240.0; L0603
I1: 2.5e-06; DR1040
R2: 1000.0; R0603
R4: 4700.0; R0603
R5, R6, R7, R8, R9, R10, R11, R12, R13, R14, R15, R16, R17, R24, R25, R30: 10000.0; R0603
R18, R19, R20: 47000.0; R0603
R21: 680.0; R0603
R22: 220000.0; R0603
R23: 1000000.0; R0603
R26: 9100.0; R0603
R27: 680000.0; R0603
R28: 120000.0; R0603
R29: 2000.0; R0603
U1: STM32F469ZIT6; LQFP144
U2: AT25010B-SSHL-T; SOIC-8
U3: AT25040B-SSHL-T; SOIC-8
U4: CY62147GE30-45BVXI; VFBGA48
U5: TST-110-05-T-D-RA
U6: 10118193-0001LF; FCI_10118193-0001LF
U7: prtr5v0u2ax; SOT143B
U8: WM8731CLSEFL; QFN-28
U9, U10: SJ-43515TS-SMT-TR
U11: ABLS-12.288MHZ-B4-T
U12: ASEK-32.768KHz-ECST; ASEK
U13: ASFL1-25MHZ-NCS; ASFL1
U14: ltc3406es5; TSOT-23-5
U15: MCP73831T-2ACI/MC; DFN8_2X3MC
U16: S2B-PH-SM4-TB(LF)(SN); JST-2-SMD
U17: TPS3895ADRYR; SON-6
U18: 4-1437565-2; SW_4-1437565-2
U19: Q65110A2395; LGM67K-G1J2-24-Z
U20, U21: nc7sz125m5x; NC7SZ125M5X

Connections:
CLK_CRYSTAL_U8_1: C40.1, U8.1, U11.1
CLK_CRYSTAL_U8_2: C41.1, U8.2, U11.2
CLK_U1_7: U1.7, U12.3
CLK_U1_18: U1.18, U13.3
GND: C1.2, C2.2, C3.2, C4.2, C5.2, C6.2, C7.2, C8.2, C9.2, C10.2, C11.2, C12.2, C13.2, C14.2, C15.2, C16.2, C17.2, C18.2, C19.2, C20.2, C21.2, C22.2, C23.2, C24.2, C25.2, C29.2, C30.2, C31.2, C32.2, C33.2, C34.2, C35.2, C36.2, C37.2, C38.2, C39.2, C40.2, C41.2, C42.2, C43.2, C44.2, C45.1, C45.2, C46.2, C47.2, C48.2, C49.2, C50.2, R2.2, R18.2, R19.2, R20.2, R22.2, R26.2, R28.2, R29.2, U1.15, U1.26, U1.33, U1.55, U1.76, U1.84, U1.105, U1.109, U1.122, U1.129, U2.4, U3.4, U4.D1, U4.E6, U5.4, U5.6, U5.8, U5.10, U5.12, U5.14, U5.16, U5.18, U5.20, U6.5, U6.6, U6.7, U6.8, U6.9, U7.1, U8.4, U8.15, U8.19, U8.25, U8.26, U8.29, U9.1, U10.1, U12.2, U13.2, U14.2, U15.6, U15.9, U16.2, U17.2, U19.C, U20.2, U20.3, U21.1, U21.3
INPUT_USBPOWER_5V: C20.1, C47.1, R30.2, U1.103, U6.1, U7.4, U15.1, U15.2
NET_U1_20: R4.1, U1.20, U21.4
NET_U1_28: C17.1, C18.1, F1.1, U1.27, U1.28
NET_U1_43: R7.1, U1.43
NET_U1_65: C15.1, U1.65
NET_U1_108: C16.1, U1.108
NET_U1_137: R6.1, U1.137
NET_U1_142: R5.1, U1.142
NET_U1_144: U18.3, U18.4
NET_U2_3: R8.1, U2.3
NET_U2_7: R10.1, U2.7
NET_U3_3: R11.1, U3.3
NET_U3_7: R13.1, U3.7
NET_U8_20: C34.1, C39.1, U8.20
NET_U9_2: C27.1, R19.1, U9.2
NET_U9_5: C26.1, R18.1, U9.5
NET_U10_5: C28.1, C29.1, R20.1, R21.1, U10.5
NET_U14_3: I1.1, U14.3
NET_U14_5: R22.1, R23.1, U14.5
NET_U14_ATNET_3: I1.2, R23.2
NET_U15_5: R30.1, U15.5
NET_U15_8: R29.1, U15.8
NET_U17_1: R25.1, R26.1, U17.1
NET_U17_3: R27.2, R28.1, U17.3
NET_U17_4: R24.1, U17.4, U20.4, U21.2
NET_U18_1: R2.1, U18.1, U18.2
PROC_FMC_A0: U1.9, U4.A3
PROC_FMC_A1: U1.10, U4.A4
PROC_FMC_A2: U1.11, U4.A5
PROC_FMC_A3: U1.12, U4.B3
PROC_FMC_A4: U1.13, U4.B4
PROC_FMC_A5: U1.14, U4.C3
PROC_FMC_A6: U1.45, U4.C4
PROC_FMC_A7: U1.47, U4.D4
PROC_FMC_A8: U1.48, U4.H2
PROC_FMC_A9: U1.49, U4.H3
PROC_FMC_A10: U1.50, U4.H4
PROC_FMC_A11: U1.51, U4.H5
PROC_FMC_A12: U1.90, U4.G3
PROC_FMC_A13: U1.91, U4.G4
PROC_FMC_A14: U1.92, U4.F3
PROC_FMC_A15: U1.93, U4.F4
PROC_FMC_A16: U1.74, U4.E4
PROC_FMC_A17: U1.75, U4.D3
PROC_FMC_D0: U1.78, U4.B6
PROC_FMC_D1: U1.79, U4.C5
PROC_FMC_D2: U1.116, U4.C6
PROC_FMC_D3: U1.117, U4.D5
PROC_FMC_D4: U1.52, U4.E5
PROC_FMC_D5: U1.53, U4.F5
PROC_FMC_D6: U1.54, U4.F6
PROC_FMC_D7: U1.57, U4.G6
PROC_FMC_D8: U1.58, U4.B1
PROC_FMC_D9: U1.59, U4.C1
PROC_FMC_D10: U1.60, U4.C2
PROC_FMC_D11: U1.61, U4.D2
PROC_FMC_D12: U1.62, U4.E2
PROC_FMC_D13: U1.71, U4.F2
PROC_FMC_D14: U1.72, U4.F1
PROC_FMC_D15: U1.73, U4.G1
PROC_FMC_NBL0: U1.140, U4.A1
PROC_FMC_NE2: R15.1, U1.125, U4.B5
PROC_FMC_NOE: R14.1, U1.120, U4.A2
PROC_FMC_NWE: R16.1, U1.121, U4.G5
PROC_I2S2_CK: U1.63, U8.7
PROC_I2S2_EXT_SD: U1.23, U8.10
PROC_I2S2_SD: U1.22, U8.8
PROC_I2S2_WS: U1.67, U8.9, U8.11
PROC_SPI1_MISO: U1.37, U3.2
PROC_SPI1_MOSI: U1.38, U3.5
PROC_SPI1_NSS: R12.1, U1.35, U3.1
PROC_SPI1_SCK: U1.36, U3.6
PROC_SPI2_MISO: U1.69, U2.2
PROC_SPI2_MOSI: U1.24, U2.5
PROC_SPI2_NSS: R9.1, U1.139, U2.1
PROC_SPI2_SCK: U1.68, U2.6
PROC_SYS_JTCK_SWCLK: U1.111, U5.9
PROC_SYS_JTDO_SWO: U1.132, U5.13
PROC_SYS_JTMS_SWDIO: U1.107, U5.7
PROC_USB_OTG_FS_DM: U1.105, U6.2, U7.3
PROC_USB_OTG_FS_DP: U1.106, U6.3, U7.2
RST_OUT_U5_SRESET_B: R17.1, U5.15, U20.1
VCC_S1_3V7: C44.1, C48.1, U14.4, U15.3, U15.4, U16.1
VCC_TIER1_3V3: C1.1, C2.1, C3.1, C4.1, C5.1, C6.1, C7.1, C8.1, C9.1, C10.1, C11.1, C12.1, C13.1, C14.1, C19.1, C21.1, C22.1, C23.1, C24.1, C25.1, C30.1, C31.1, C32.1, C33.1, C35.1, C36.1, C37.1, C38.1, C42.1, C43.1, C45.2, C46.1, C49.1, C50.1, F1.2, I1.2, R4.2, R5.2, R6.2, R7.2, R8.2, R9.2, R10.2, R11.2, R12.2, R13.2, R14.2, R15.2, R16.2, R17.2, R23.2, R24.2, R25.2, R27.1, U1.5, U1.16, U1.25, U1.34, U1.46, U1.56, U1.66, U1.77, U1.80, U1.97, U1.110, U1.123, U1.130, U1.143, U2.8, U3.8, U4.D6, U4.E1, U5.1, U8.3, U8.5, U8.12, U8.18, U12.4, U13.4, U17.6, U20.5, U21.5
